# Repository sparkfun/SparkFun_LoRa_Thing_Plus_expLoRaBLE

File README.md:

SparkFun LoRa Thing Plus - expLoRaBLE
========================================

[*SparkFun LoRa Thing Plus - expLoRaBLE (WRL-17506)*](https://www.sparkfun.com/products/17506)

The SparkFun LoRa Thing Plus - expLoRaBLE is a wireless development board in Thing Plus form factor that includes the NM180100 LoRa® Bluetooth® 5 Low Energy SiP. It is a global IoT solution ideal for long range, low power applications combining the transmit power of Semtech's LoRa® SX1262 with the processing power of Ambiq Micro's Apollo3 Blue.

Repository Contents
-------------------

* **/Documentation** - Data sheets, additional product information
* **/Hardware** - Eagle design files (.brd, .sch)
* **/Hardware/Production** - Production panel files (.brd)

Documentation
--------------
* **[Hookup Guide](https://learn.sparkfun.com/tutorials/sparkfun-explorable-hookup-guide)** - Basic hookup guide for the [LoRa Thing Plus - expLoRaBLE](https://www.sparkfun.com/products/17506).

License Information
-------------------

This product is _**open source**_! 

Please review the LICENSE.md file for license information. 

If you have any questions or concerns on licensing, please contact technical support on our [SparkFun forums](https://forum.sparkfun.com/viewforum.php?f=152).

Distributed as-is; no warranty is given.

- Your friends at SparkFun.

_<COLLABORATION CREDIT>_

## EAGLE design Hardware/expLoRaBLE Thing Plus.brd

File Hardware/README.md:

SparkFun LoRa Thing Plus - expLoRaBLE Design Files
=====================================

The .sch and .brd files hare are Eagle CAD schematic and PCB design files from SparkFun Electronics.
A freeware version of Autodesk Eagle can be found [here](https://www.autodesk.com/products/eagle/free-download).

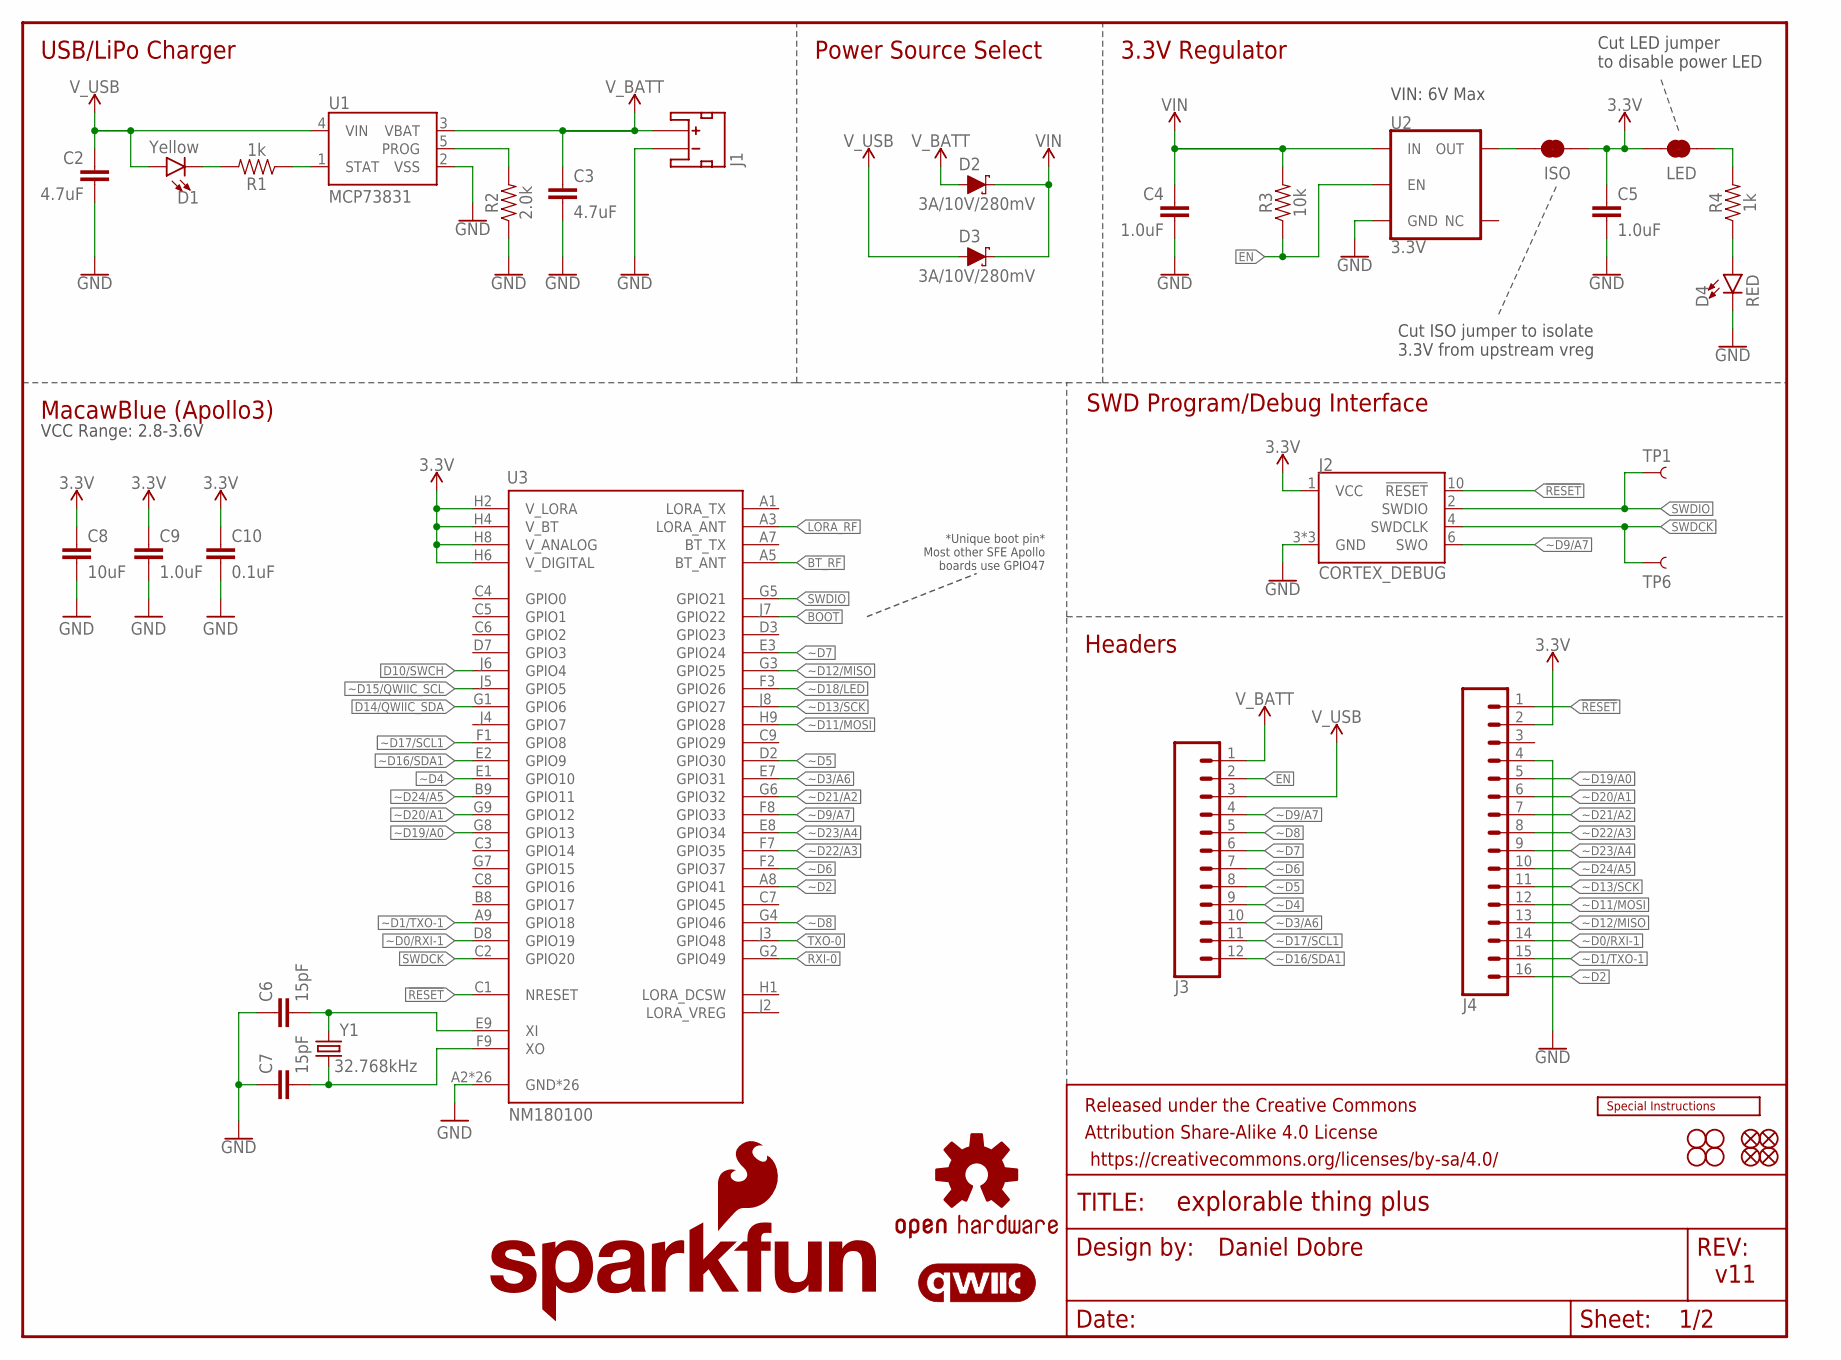
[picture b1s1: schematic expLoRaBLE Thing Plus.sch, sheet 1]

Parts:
C2, C3: 4.7uF; 0603
C4, C5, C9: 1.0uF; 0603
C6, C7: 15pF; 0603
C8: 10uF; 0603
C10: 0.1uF; 0603
D1: Yellow; LED-0603
D2, D3: 3A/10V/280mV; SOD-323
D4: RED; LED-0603
FD1, FD2, FD3, FD4: FIDUCIALUFIDUCIAL; FIDUCIAL-MICRO
FRAME1: FRAME-LETTER; CREATIVE_COMMONS
H1, H2, H3, H4: STAND-OFF
ISO: JUMPER-SMT_2_NC_TRACE_SILK; SMT-JUMPER_2_NC_TRACE_SILK
J1: JST_2MM_MALE; JST-2-SMD
J2: CORTEX_DEBUG; 2X5-PTH-1.27MM-NO_SILK
J3: CONN_12SM_SQ_NO_SILK; 1X12_SM_SQ_NOSILK
J4: CONN_161X16_SM_SQ_NOSILK; 1X16_SM_SQ_NOSILK
LED: JUMPER-SMT_2_NC_TRACE_SILK; SMT-JUMPER_2_NC_TRACE_SILK
LOGO1: OSHW-LOGOS; OSHW-LOGO-S
LOGO2: QWIIC_LOGO_5MM; QWIIC_5MM
LOGO3: SFE_LOGO_NAME_FLAME.1_INCH; SFE_LOGO_NAME_FLAME_.1
LOGO4: SPECIAL_INSTRUCTIONS-ORDERING; ORDERING_INSTRUCTIONS
R1, R4: 1k; 0603
R2: 2.0k; 0603
R3: 10k; 0603
TP1, TP6: TEST-POINTTP_15TH_THRU; TP_15TH
U1: MCP73831; SOT23-5
U2: 3.3V; SOT23-5
U3: NM180100; LGA81
Y1: 32.768kHz; CRYSTAL-SMD-3.2X1.5MM

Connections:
3.3V: C5.1, C8.1, C9.1, C10.1, ISO.1, J2.1 (VCC), J4.2, LED.2, U3.H2 (V_LORA), U3.H4 (V_BT), U3.H6 (V_DIGITAL), U3.H8 (V_ANALOG); also elsewhere on the board
!RESET: J2.10 (!RESET), J4.1, U3.C1 (NRESET); also elsewhere on the board
BOOT: U3.J7 (GPIO22); also elsewhere on the board
BT_RF: U3.A5 (BT_ANT); also elsewhere on the board
D10/SWCH: U3.J6 (GPIO4); also elsewhere on the board
D14/QWIIC_SDA: U3.G1 (GPIO6); also elsewhere on the board
EN: J3.2, R3.1, U2.3 (EN)
GND: C2.2, C3.2, C4.2, C5.2, C6.1, C7.1, C8.2, C9.2, C10.2, D4.C, J1.1 (-), J2.3 (GND), J2.5 (GND), J2.9 (GND), J4.4, R2.1, U1.2 (VSS), U2.2 (GND), U3.A2 (GND*26), U3.A4 (GND*26), U3.A6 (GND*26), U3.B1 (GND*26), U3.B2 (GND*26), U3.B3 (GND*26), U3.B4 (GND*26), U3.B5 (GND*26), U3.B6 (GND*26), U3.B7 (GND*26), U3.D1 (GND*26), U3.D4 (GND*26), U3.D5 (GND*26), U3.D6 (GND*26), U3.D9 (GND*26), U3.E4 (GND*26), U3.E5 (GND*26), U3.E6 (GND*26), U3.F4 (GND*26), U3.F5 (GND*26), U3.F6 (GND*26), U3.H3 (GND*26), U3.H5 (GND*26), U3.H7 (GND*26), U3.J1 (GND*26), U3.J9 (GND*26); also elsewhere on the board
LORA_RF: U3.A3 (LORA_ANT); also elsewhere on the board
unnamed: R2.2, U1.5 (PROG)
unnamed: C7.2, U3.F9 (XO), Y1.P$2 (2)
unnamed: D1.C, R1.2
unnamed: R1.1, U1.1 (STAT)
unnamed: LED.1, R4.2
unnamed: C6.2, U3.E9 (XI), Y1.P$1 (1)
unnamed: D4.A, R4.1
unnamed: ISO.2, U2.5 (OUT)
RXI-0: U3.G2 (GPIO49); also elsewhere on the board
SWDCK: J2.4 (SWDCLK), TP6.P$1, U3.C2 (GPIO20)
SWDIO: J2.2 (SWDIO), TP1.P$1, U3.G5 (GPIO21)
TXO-0: U3.J3 (GPIO48); also elsewhere on the board
VIN: C4.1, D2.C, D3.C, R3.2, U2.1 (IN)
V_BATT: C3.1, D2.A, J1.2 (+), J3.1, U1.3 (VBAT)
V_USB: C2.1, D1.A, D3.A, J3.3, U1.4 (VIN); also elsewhere on the board
~D0/RXI-1: J4.14, U3.D8 (GPIO19)
~D1/TXO-1: J4.15, U3.A9 (GPIO18)
~D2: J4.16, U3.A8 (GPIO41)
~D3/A6: J3.10, U3.E7 (GPIO31)
~D4: J3.9, U3.E1 (GPIO10)
~D5: J3.8, U3.D2 (GPIO30)
~D6: J3.7, U3.F2 (GPIO37)
~D7: J3.6, U3.E3 (GPIO24)
~D8: J3.5, U3.G4 (GPIO46)
~D9/A7: J2.6 (SWO), J3.4, U3.F8 (GPIO33)
~D11/MOSI: J4.12, U3.H9 (GPIO28)
~D12/MISO: J4.13, U3.G3 (GPIO25)
~D13/SCK: J4.11, U3.J8 (GPIO27)
~D15/QWIIC_SCL: U3.J5 (GPIO5); also elsewhere on the board
~D16/SDA1: J3.12, U3.E2 (GPIO9)
~D17/SCL1: J3.11, U3.F1 (GPIO8)
~D18/LED: U3.F3 (GPIO26); also elsewhere on the board
~D19/A0: J4.5, U3.G8 (GPIO13)
~D20/A1: J4.6, U3.G9 (GPIO12)
~D21/A2: J4.7, U3.G6 (GPIO32)
~D22/A3: J4.8, U3.F7 (GPIO35)
~D23/A4: J4.9, U3.E8 (GPIO34)
~D24/A5: J4.10, U3.B9 (GPIO11)

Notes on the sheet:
SWD Program/Debug Interface
Headers
MacawBlue (Apollo3)
USB/LiPo Charger
Power Source Select
3.3V Regulator
VIN: 6V Max
Daniel Dobre
v11
Cut LED jumper to disable power LED
Cut ISO jumper to isolate 3.3V from upstream vreg
VCC Range: 2.8-3.6V
*Unique boot pin* Most other SFE Apollo boards use GPIO47

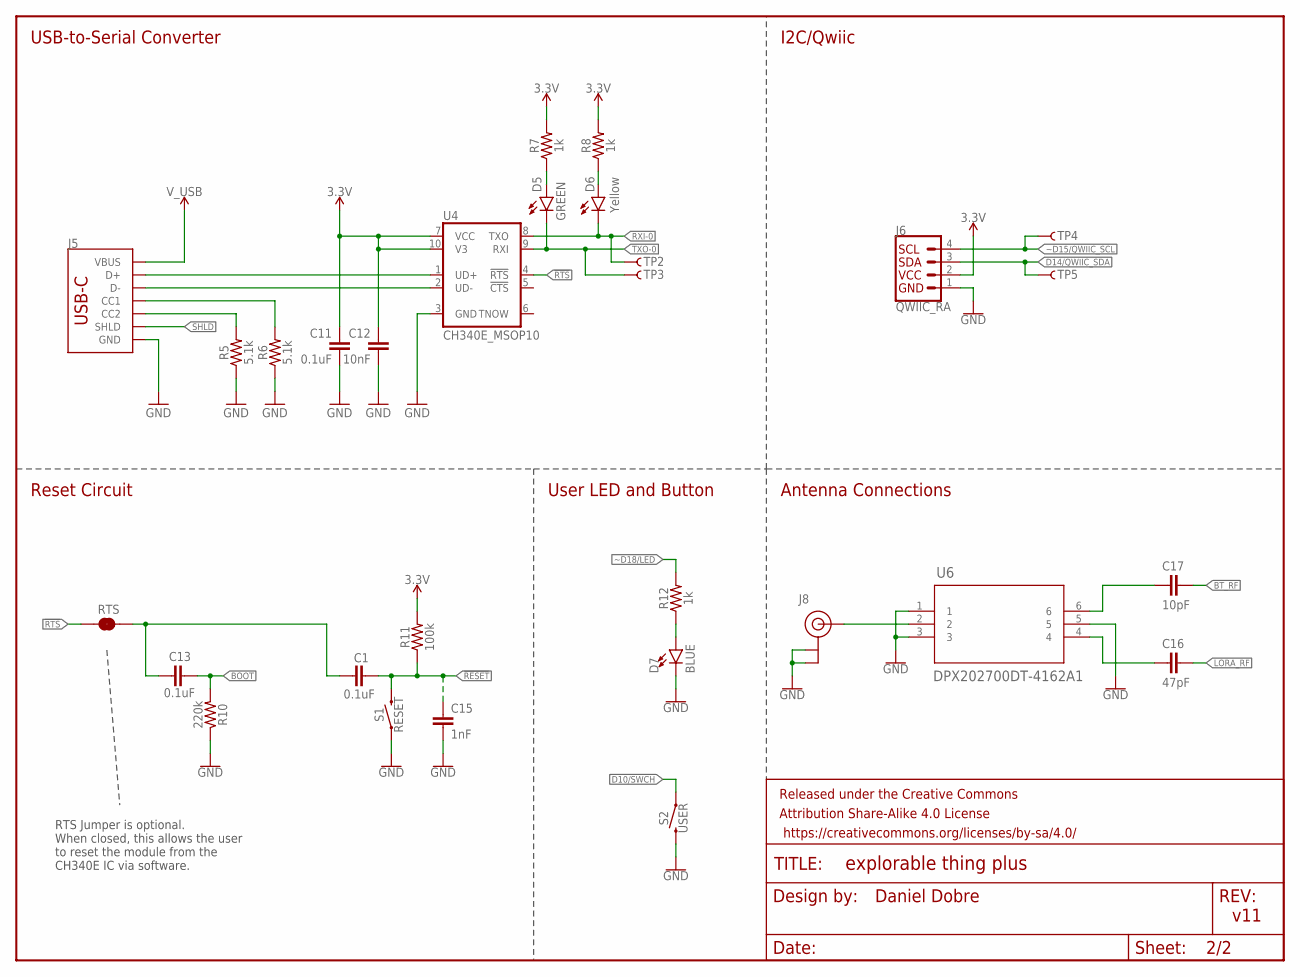
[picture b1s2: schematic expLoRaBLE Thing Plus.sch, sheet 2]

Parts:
C1, C11, C13: 0.1uF; 0603
C12: 10nF; 0603
C15: 1nF; 0603
C16: 47pF; 0603
C17: 10pF; 0603
D5: GREEN; LED-0603
D6: Yellow; LED-0603
D7: BLUE; LED-0603
FRAME2: FRAME-LETTERNO_PACKAGE; DUMMY
J5: USB Female Type C Connector; USB-C-16P-4LAYER-ISOLATED
J6: QWIIC_RA; JST04_1MM_RA
J8: U.FL
R5, R6: 5.1k; 0603
R7, R8, R12: 1k; 0603
R10: 220k; 0603
R11: 100k; 0603
RTS: JUMPER-SMT_2_NC_TRACE_SILK; SMT-JUMPER_2_NC_TRACE_SILK
S1: RESET; TACTILE_SWITCH_SMD_4.6X2.8MM
S2: USER; TACTILE_SWITCH_SMD_4.6X2.8MM
TP2, TP3, TP4, TP5: TEST-POINTTP_15TH_THRU; TP_15TH
U4: CH340E_MSOP10; MSOP10
U6: DPX202700DT-4162A1; RF_4060A1_TDK

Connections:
3.3V: C11.1, C12.1, J6.2, R7.2, R8.2, R11.2, U4.7 (VCC), U4.10 (V3); also elsewhere on the board
!RESET: C1.2, C15.1, R11.1, S1.3 (2), S1.4 (2); also elsewhere on the board
!RTS: RTS.1, U4.4 (!RTS)
BOOT: C13.2, R10.2; also elsewhere on the board
BT_RF: C17.1; also elsewhere on the board
CC1: J5.A5 (CC1), R6.2
CC2: J5.B5 (CC2), R5.2
D10/SWCH: S2.1, S2.2 (1); also elsewhere on the board
D14/QWIIC_SDA: J6.3, TP5.P$1; also elsewhere on the board
D+1: J5.A6 (D+), J5.B6 (D+), U4.1 (UD+)
D-1: J5.A7 (D-), J5.B7 (D-), U4.2 (UD-)
GND: C11.2, C12.2, C15.2, D7.C, J5.GND, J5.GND2 (GND), J6.1, J8.1 (GND), J8.2 (GND), R5.1, R6.1, R10.1, S1.1, S1.2 (1), S2.3 (2), S2.4 (2), U4.3 (GND), U6.1, U6.3, U6.5; also elsewhere on the board
LORA_RF: C16.1; also elsewhere on the board
unnamed: D5.A, R7.1
unnamed: D7.A, R12.1
unnamed: D6.A, R8.1
unnamed: C17.2, U6.6
unnamed: J8.FEED (SIGNAL), U6.2
unnamed: C16.2, U6.4
unnamed: C1.1, C13.1, RTS.2
RXI-0: D6.C, TP2.P$1, U4.8 (TXO); also elsewhere on the board
SHLD: J5.SHLD1 (SHLD), J5.SHLD2 (SHLD), J5.SHLD3 (SHLD), J5.SHLD4 (SHLD), J5.SHLD5 (SHLD), J5.SHLD6 (SHLD), J5.SHLD7 (SHLD), J5.SHLD8 (SHLD)
TXO-0: D5.C, TP3.P$1, U4.9 (RXI); also elsewhere on the board
V_USB: J5.VBUS1 (VBUS), J5.VBUS2 (VBUS); also elsewhere on the board
~D15/QWIIC_SCL: J6.4, TP4.P$1; also elsewhere on the board
~D18/LED: R12.2; also elsewhere on the board

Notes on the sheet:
Antenna Connections
USB-to-Serial Converter
Reset Circuit
User LED and Button
I2C/Qwiic
Daniel Dobre
v11
RTS Jumper is optional. When closed, this allows the user to reset the module from the CH340E IC via software.

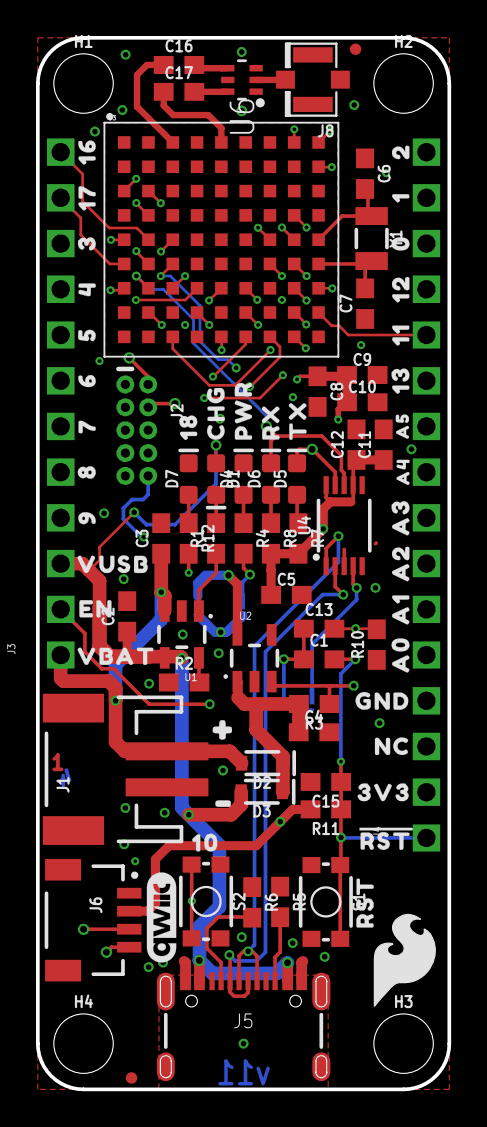
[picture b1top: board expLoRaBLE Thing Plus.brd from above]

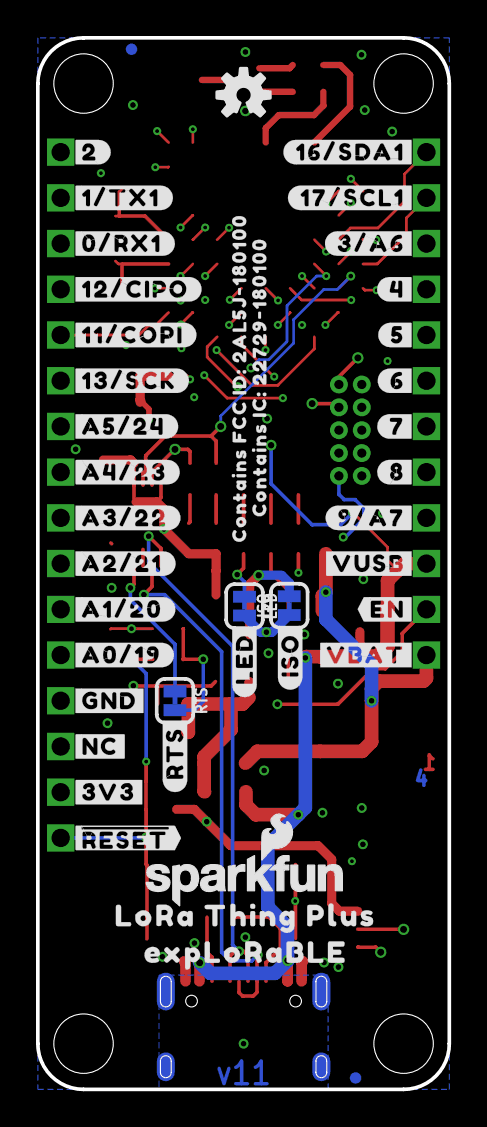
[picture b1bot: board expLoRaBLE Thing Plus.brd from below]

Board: 4 copper layers, 22.9 x 58.4 mm, 146 parts (42 on the bottom side), 60 nets.

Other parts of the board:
U$1: #16#SDA1#0
U$2: LORA_THING_PLUS0
U$3: EXPLORABLE0
U$4: #17#SCL1#0
U$5: #3#A6#0
U$6: #4#0
U$7: #5#0
U$8: #6#0
U$9: #7#0
U$10: #8#0
U$11: #9#A7#0
U$12: #VUSB#0
U$13: VUSB0
U$14: #EN#0
U$15: #VBAT#0
U$16: #2#0
U$17: #1#TX1#0
U$18: #0#RX1#0
U$19: #12#CIPO#0
U$20: #11#COPI#0
U$21: #13#SCK#0
U$22: CONTAINS_FCC_ID#_2AL5J#1801000
U$23: CONTAINS_IC#_22729#1801000
U$24: #RTS#0
U$28: #GND#0
U$29: #NC#0
U$30: #3V3#0
U$31: ##RESET##0
U$32: #LED#0
U$33: #A0#19#0
U$34: #ISO#0
U$35: #A1#20#0
U$36: #A2#21#0
U$37: #A3#22#0
U$38: #A4#23#0
U$39: #A5#24#0
U$62: 180
U$64: FOUR_LAYER_WARNING
U$65: SFE_LOGO_FLAME_.2
U$66: 160
U$67: CHG0
U$68: PWR0
U$69: 170
U$70: 30
U$71: 40
U$72: 50
U$73: 60
U$74: 70
U$75: 80
U$76: 90
U$78: EN0
U$79: VBAT0
U$80: 20
U$81: 10
U$82: 00
U$83: 120
U$84: 110
U$85: 130
U$86: A50
U$87: A40
U$88: A30
U$89: A20
U$90: A10
U$91: A00
U$92: GND0
U$93: NC0
U$94: 3V30
U$95: #RST#0
U$96: RST0
U$97: 100
U$98: #0
U$99: #_0
U$100: RX0
U$101: TX0

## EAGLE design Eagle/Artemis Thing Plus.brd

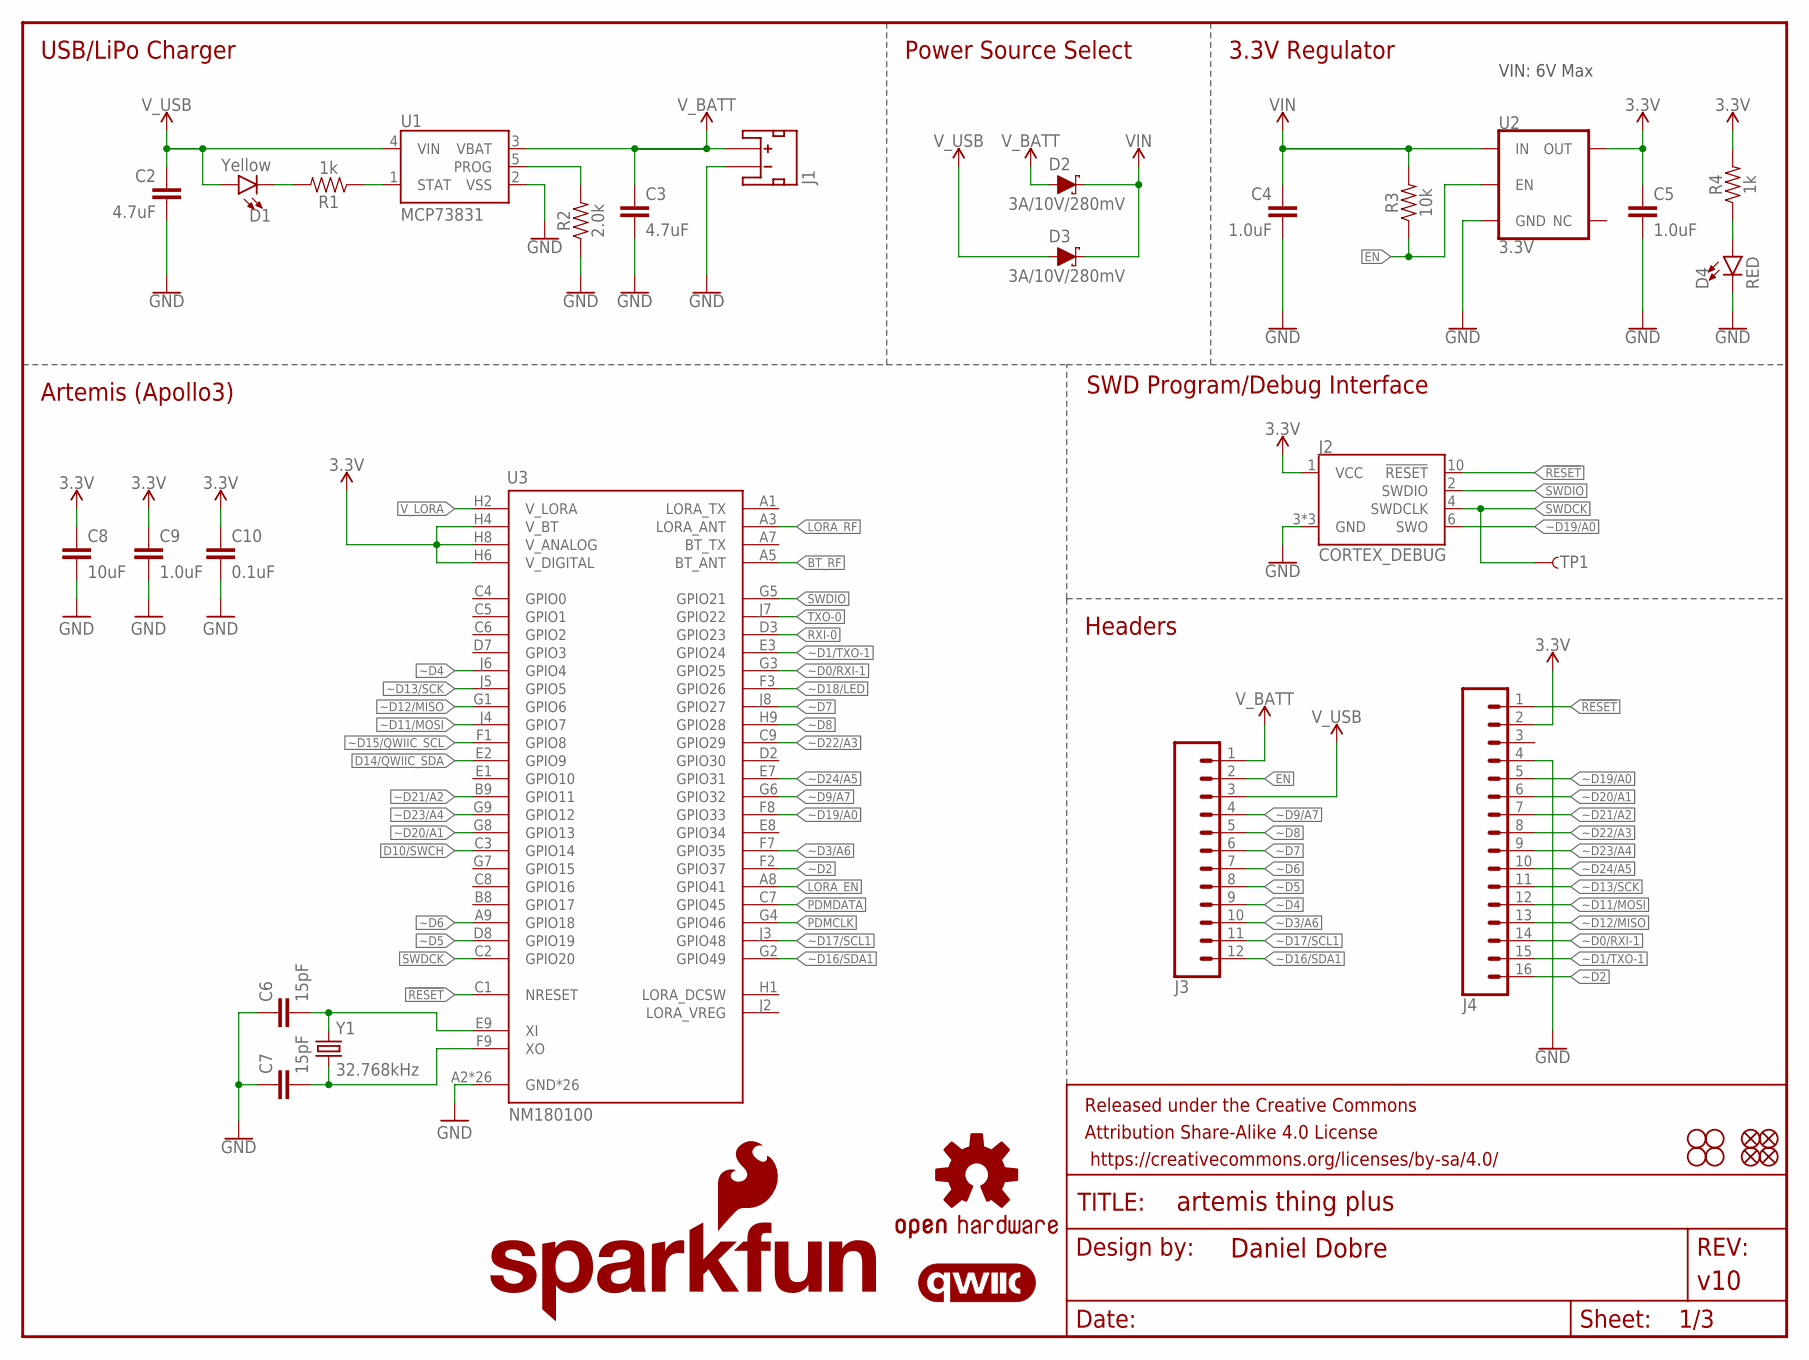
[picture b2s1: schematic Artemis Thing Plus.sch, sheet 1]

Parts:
C2, C3: 4.7uF; 0603
C4, C5: 1.0uF; 0402-TIGHT
C6, C7: 15pF; 0603
C8: 10uF; 0603
C9: 1.0uF; 0603
C10: 0.1uF; 0603
D1: Yellow; LED-0603
D2, D3: 3A/10V/280mV; SOD-323
D4: RED; LED-0603
FD1, FD2, FD3, FD4: FIDUCIALUFIDUCIAL; FIDUCIAL-MICRO
FRAME1: FRAME-LETTER; CREATIVE_COMMONS
H1, H2, H3, H4: STAND-OFF
J1: JST_2MM_MALE; JST-2-SMD
J2: CORTEX_DEBUG; 2X5-PTH-1.27MM-NO_SILK
J3: CONN_12SM_SQ_NO_SILK; 1X12_SM_SQ_NOSILK
J4: CONN_161X16_SM_SQ_NOSILK; 1X16_SM_SQ_NOSILK
LOGO1: OSHW-LOGOS; OSHW-LOGO-S
LOGO2: QWIIC_LOGO_5MM; QWIIC_5MM
LOGO3: SFE_LOGO_NAME_FLAME.1_INCH; SFE_LOGO_NAME_FLAME_.1
R1, R4: 1k; 0603
R2: 2.0k; 0603
R3: 10k; 0603
TP1: TEST-POINTTP_15TH_THRU; TP_15TH
U1: MCP73831; SOT23-5
U2: 3.3V; SOT23-5
U3: NM180100; LGA81
Y1: 32.768kHz; CRYSTAL-SMD-3.2X1.5MM

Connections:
3.3V: C5.1, C8.1, C9.1, C10.1, J2.1 (VCC), J4.2, R4.2, U2.5 (OUT), U3.H4 (V_BT), U3.H6 (V_DIGITAL), U3.H8 (V_ANALOG); also elsewhere on the board
!RESET: J2.10 (!RESET), J4.1, U3.C1 (NRESET); also elsewhere on the board
BT_RF: U3.A5 (BT_ANT); also elsewhere on the board
D10/SWCH: U3.C3 (GPIO14); also elsewhere on the board
D14/QWIIC_SDA: U3.E2 (GPIO9); also elsewhere on the board
EN: J3.2, R3.1, U2.3 (EN)
GND: C2.2, C3.2, C4.2, C5.2, C6.1, C7.1, C8.2, C9.2, C10.2, D4.C, J1.1 (-), J2.3 (GND), J2.5 (GND), J2.9 (GND), J4.4, R2.1, U1.2 (VSS), U2.2 (GND), U3.A2 (GND*26), U3.A4 (GND*26), U3.A6 (GND*26), U3.B1 (GND*26), U3.B2 (GND*26), U3.B3 (GND*26), U3.B4 (GND*26), U3.B5 (GND*26), U3.B6 (GND*26), U3.B7 (GND*26), U3.D1 (GND*26), U3.D4 (GND*26), U3.D5 (GND*26), U3.D6 (GND*26), U3.D9 (GND*26), U3.E4 (GND*26), U3.E5 (GND*26), U3.E6 (GND*26), U3.F4 (GND*26), U3.F5 (GND*26), U3.F6 (GND*26), U3.H3 (GND*26), U3.H5 (GND*26), U3.H7 (GND*26), U3.J1 (GND*26), U3.J9 (GND*26); also elsewhere on the board
LORA_EN: U3.A8 (GPIO41); also elsewhere on the board
LORA_RF: U3.A3 (LORA_ANT); also elsewhere on the board
unnamed: R2.2, U1.5 (PROG)
unnamed: C7.2, U3.F9 (XO), Y1.P$2 (2)
unnamed: D1.C, R1.2
unnamed: R1.1, U1.1 (STAT)
unnamed: C6.2, U3.E9 (XI), Y1.P$1 (1)
unnamed: D4.A, R4.1
PDMCLK: U3.G4 (GPIO46)
PDMDATA: U3.C7 (GPIO45)
RXI-0: U3.D3 (GPIO23); also elsewhere on the board
SWDCK: J2.4 (SWDCLK), TP1.P$1, U3.C2 (GPIO20)
SWDIO: J2.2 (SWDIO), U3.G5 (GPIO21)
TXO-0: U3.J7 (GPIO22); also elsewhere on the board
VIN: C4.1, D2.C, D3.C, R3.2, U2.1 (IN); also elsewhere on the board
V_BATT: C3.1, D2.A, J1.2 (+), J3.1, U1.3 (VBAT)
V_LORA: U3.H2 (V_LORA); also elsewhere on the board
V_USB: C2.1, D1.A, D3.A, J3.3, U1.4 (VIN); also elsewhere on the board
~D0/RXI-1: J4.14, U3.G3 (GPIO25)
~D1/TXO-1: J4.15, U3.E3 (GPIO24)
~D2: J4.16, U3.F2 (GPIO37)
~D3/A6: J3.10, U3.F7 (GPIO35)
~D4: J3.9, U3.J6 (GPIO4)
~D5: J3.8, U3.D8 (GPIO19)
~D6: J3.7, U3.A9 (GPIO18)
~D7: J3.6, U3.J8 (GPIO27)
~D8: J3.5, U3.H9 (GPIO28)
~D9/A7: J3.4, U3.G6 (GPIO32)
~D11/MOSI: J4.12, U3.J4 (GPIO7)
~D12/MISO: J4.13, U3.G1 (GPIO6)
~D13/SCK: J4.11, U3.J5 (GPIO5)
~D15/QWIIC_SCL: U3.F1 (GPIO8); also elsewhere on the board
~D16/SDA1: J3.12, U3.G2 (GPIO49)
~D17/SCL1: J3.11, U3.J3 (GPIO48)
~D18/LED: U3.F3 (GPIO26); also elsewhere on the board
~D19/A0: J2.6 (SWO), J4.5, U3.F8 (GPIO33)
~D20/A1: J4.6, U3.G8 (GPIO13)
~D21/A2: J4.7, U3.B9 (GPIO11)
~D22/A3: J4.8, U3.C9 (GPIO29)
~D23/A4: J4.9, U3.G9 (GPIO12)
~D24/A5: J4.10, U3.E7 (GPIO31)

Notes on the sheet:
SWD Program/Debug Interface
Headers
Artemis (Apollo3)
USB/LiPo Charger
Power Source Select
3.3V Regulator
VIN: 6V Max

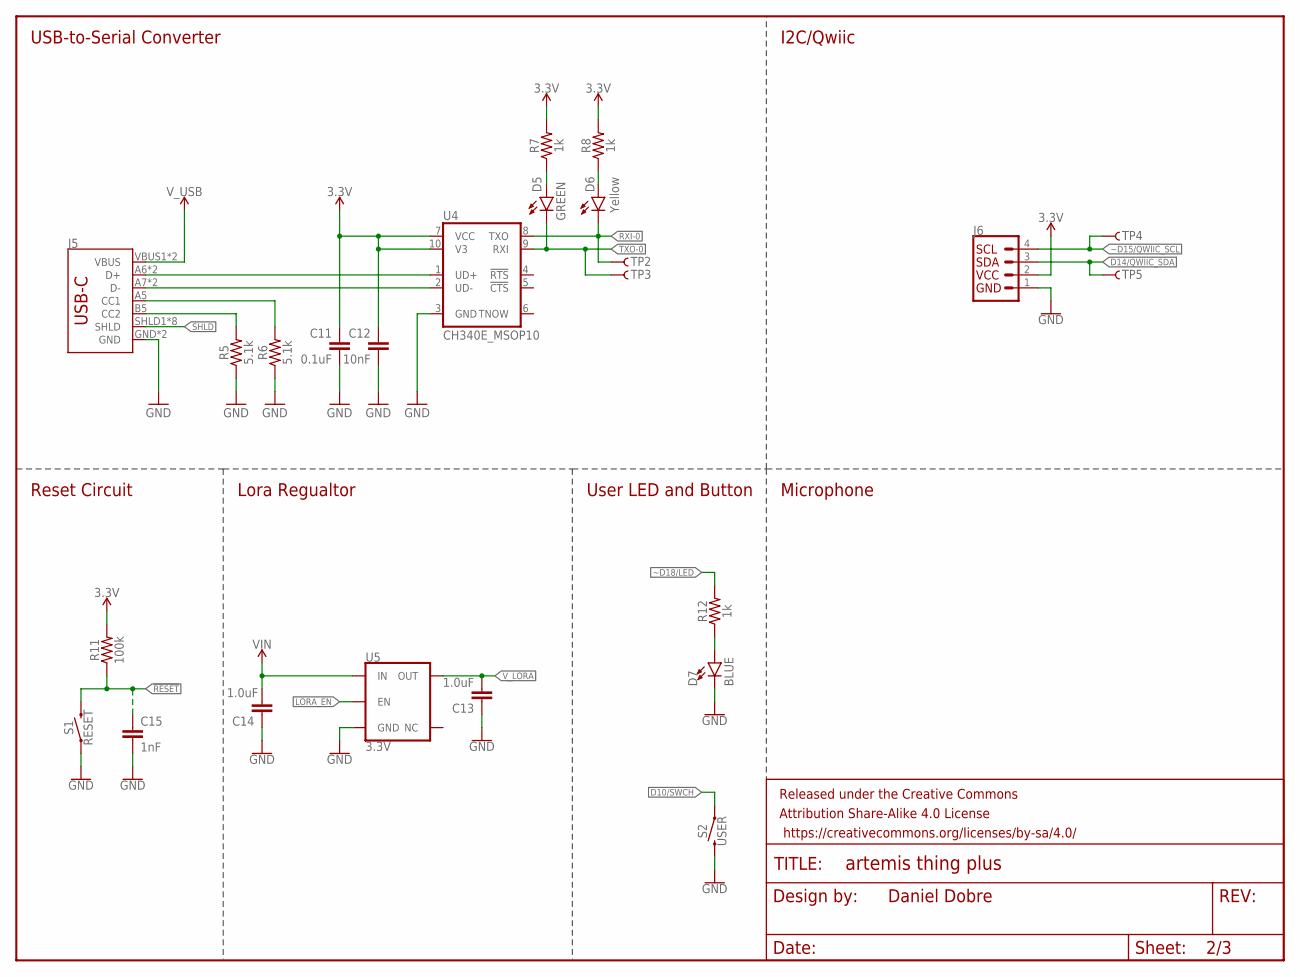
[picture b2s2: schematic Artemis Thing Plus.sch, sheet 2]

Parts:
C11: 0.1uF; 0603
C12: 10nF; 0603
C13, C14: 1.0uF; 0603
C15: 1nF; 0603
D5: GREEN; LED-0603
D6: Yellow; LED-0603
D7: BLUE; LED-0603
FRAME2: FRAME-LETTERNO_PACKAGE; DUMMY
J5: USB-C; USB-C-16P
J6: QWIIC_CONNECTORJS-1MM; JST04_1MM_RA
R5, R6: 5.1k; 0603
R7, R8, R12: 1k; 0603
R11: 100k; 0603
S1: RESET; TACTILE_SWITCH_SMD_4.6X2.8MM
S2: USER; TACTILE_SWITCH_SMD_4.6X2.8MM
TP2, TP3, TP4, TP5: TEST-POINTTP_15TH_THRU; TP_15TH
U4: CH340E_MSOP10; MSOP10
U5: 3.3V; SOT23-5

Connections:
3.3V: C11.1, C12.1, J6.2, R7.2, R8.2, R11.2, U4.7 (VCC), U4.10 (V3); also elsewhere on the board
!RESET: C15.1, R11.1, S1.3 (2), S1.4 (2); also elsewhere on the board
CC1: J5.A5 (CC1), R6.2
CC2: J5.B5 (CC2), R5.2
D10/SWCH: S2.1, S2.2 (1); also elsewhere on the board
D14/QWIIC_SDA: J6.3, TP5.P$1; also elsewhere on the board
D+1: J5.A6 (D+), J5.B6 (D+), U4.1 (UD+)
D-1: J5.A7 (D-), J5.B7 (D-), U4.2 (UD-)
GND: C11.2, C12.2, C13.1, C14.1, C15.2, D7.C, J5.GND, J5.GND2 (GND), J6.1, R5.1, R6.1, S1.1, S1.2 (1), S2.3 (2), S2.4 (2), U4.3 (GND), U5.2 (GND); also elsewhere on the board
LORA_EN: U5.3 (EN); also elsewhere on the board
unnamed: D5.A, R7.1
unnamed: D7.A, R12.1
unnamed: D6.A, R8.1
RXI-0: D6.C, TP2.P$1, U4.8 (TXO); also elsewhere on the board
SHLD: J5.SHLD1 (SHLD), J5.SHLD2 (SHLD), J5.SHLD3 (SHLD), J5.SHLD4 (SHLD), J5.SHLD5 (SHLD), J5.SHLD6 (SHLD), J5.SHLD7 (SHLD), J5.SHLD8 (SHLD)
TXO-0: D5.C, TP3.P$1, U4.9 (RXI); also elsewhere on the board
VIN: C14.2, U5.1 (IN); also elsewhere on the board
V_LORA: C13.2, U5.5 (OUT); also elsewhere on the board
V_USB: J5.VBUS1 (VBUS), J5.VBUS2 (VBUS); also elsewhere on the board
~D15/QWIIC_SCL: J6.4, TP4.P$1; also elsewhere on the board
~D18/LED: R12.2; also elsewhere on the board

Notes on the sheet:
Microphone
USB-to-Serial Converter
Reset Circuit
User LED and Button
I2C/Qwiic
Daniel Dobre
Lora Regualtor

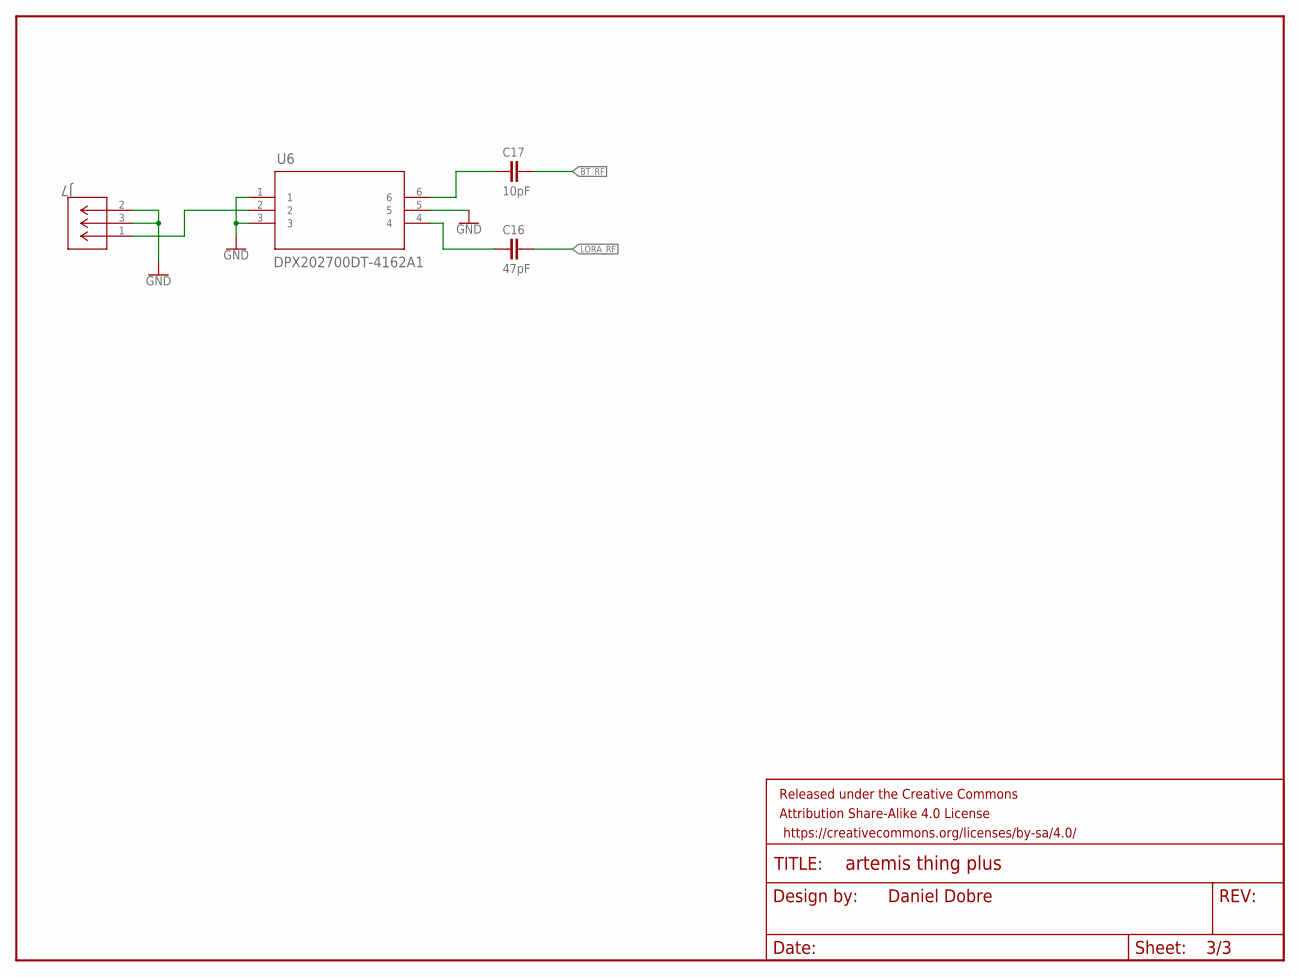
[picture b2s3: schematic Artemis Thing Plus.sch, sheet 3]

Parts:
C16: 47pF; 0603
C17: 10pF; 0603
FRAME3: FRAME-LETTERNO_PACKAGE; DUMMY
J7: U.FL-R-SMT-1(10); CONN_R-SMT-1(10)
U6: DPX202700DT-4162A1; RF_4060A1_TDK

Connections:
BT_RF: C17.1; also elsewhere on the board
GND: J7.2, J7.3, U6.1, U6.3, U6.5; also elsewhere on the board
LORA_RF: C16.1; also elsewhere on the board
unnamed: C17.2, U6.6
unnamed: J7.1, U6.2
unnamed: C16.2, U6.4

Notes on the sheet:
Daniel Dobre

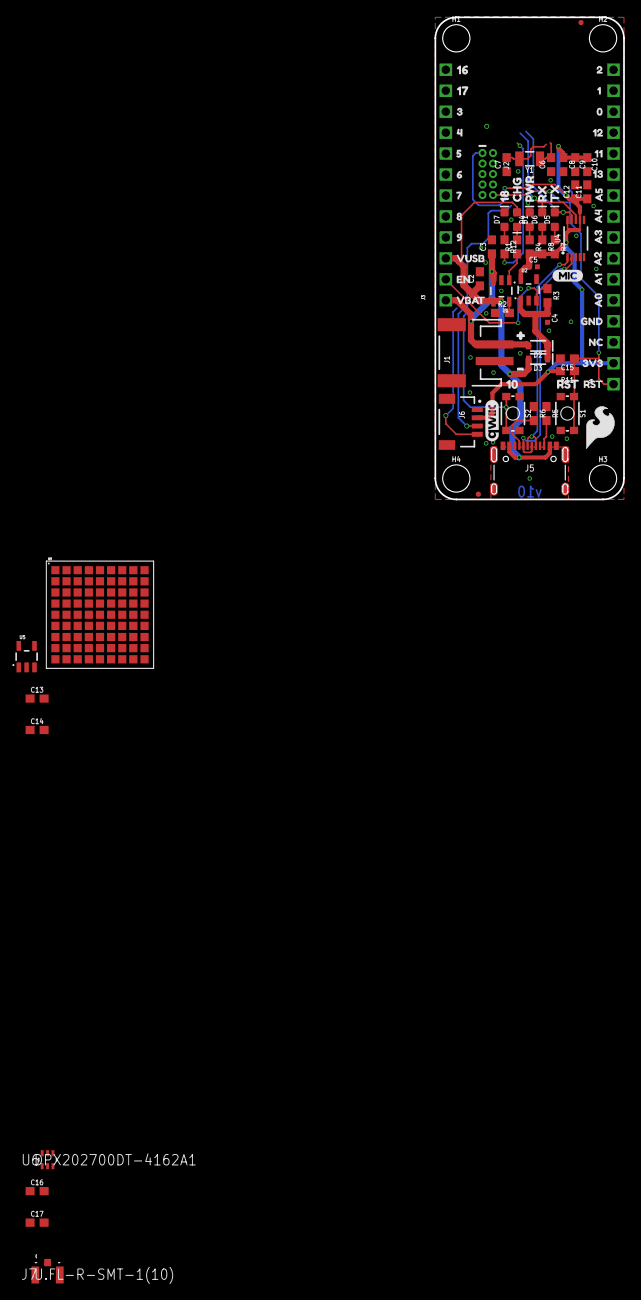
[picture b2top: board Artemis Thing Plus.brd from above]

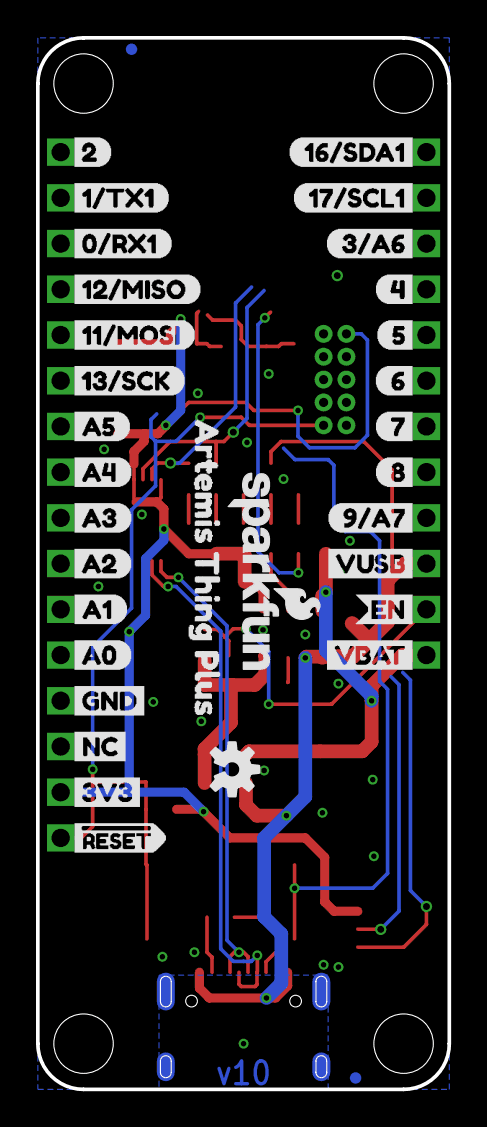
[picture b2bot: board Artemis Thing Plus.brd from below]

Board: 2 copper layers, 22.9 x 58.4 mm, 136 parts (33 on the bottom side), 57 nets.

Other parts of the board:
U$1: 160
U$2: 171
U$3: 32
U$4: 43
U$5: 54
U$6: 65
U$7: 76
U$8: 87
U$9: 98
U$10: VUSB9
U$11: EN10
U$12: VBAT11
U$13: 227
U$14: 126
U$15: 025
U$16: 1123
U$17: 1224
U$18: 1322
U$19: A521
U$20: A420
U$21: A319
U$22: A218
U$23: A117
U$24: A016
U$25: GND13
U$26: NC12
U$27, U$48: 3V314
U$28: RST15
U$29: 184
U$30: CHG1
U$31: PWR2
U$32: RX3
U$33: TX4
U$34: 20
U$35: 1#TX11
U$36: 0#RX12
U$37: 12#MISO3
U$38: 11#MOSI4
U$39: 13#SCK5
U$40: A56
U$41: A47
U$42: A38
U$43: A29
U$44: A110
U$45: A011
U$46: GND12
U$47: NC13
U$49: #RESET15
U$50: 16#SDA12
U$51: 17#SCL13
U$52: 412
U$53: 513
U$54: 614
U$55: 715
U$56: 816
U$57: 9#A719
U$58: 3#A60
U$59: VUSB25
U$60: EN26
U$61: VBAT27
U$62: 100
U$63: RST1
U$64: ARTEMIS_THING_PLUS0
U$65: SFE_LOGO_FLAME_.2
U$66: MIC0
U$67: #0
U$68: #1

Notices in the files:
parts and their libraries:
SparkFun-Capacitors: Licensing: Creative Commons ShareAlike 4.0 International - https://creativecommons.org/licenses/by-sa/4.0
SparkFun-Aesthetics: Released under the Creative Commons Attribution Share-Alike 4.0 License
SparkFun-Aesthetics: https://creativecommons.org/licenses/by-sa/4.0
